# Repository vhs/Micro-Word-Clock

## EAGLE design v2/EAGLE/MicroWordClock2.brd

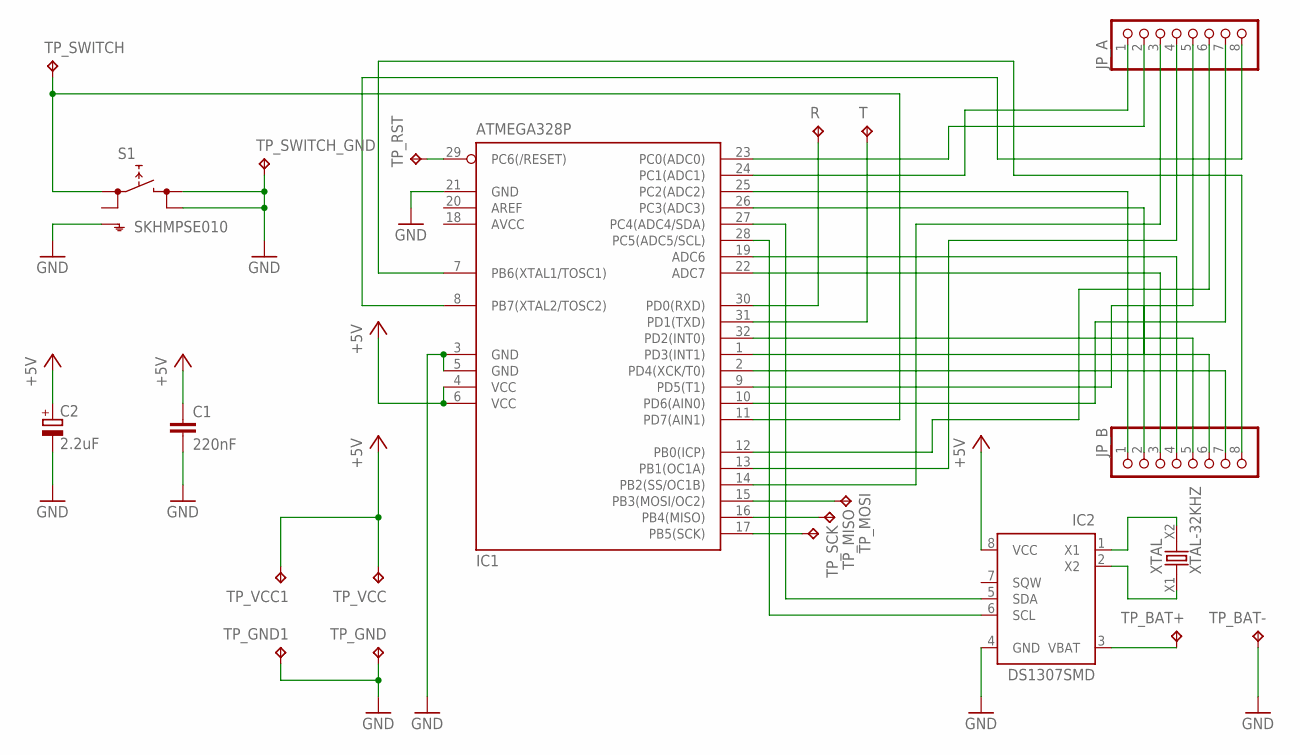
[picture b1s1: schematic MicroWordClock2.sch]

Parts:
C1: 220nF; C0805
C2: 2.2uF; B/3528-21R
IC1: ATMEGA328P; TQFP32-08
IC2: DS1307SMD; SO-08M
JP_A: PINHD-1X8CLEANBIG; 1X08-CLEANBIG
JP_B: PINHD-1X8CLEANBIG; 1X08-CLEANBIG
R: TPB1,27; B1,27
S1: SKHMPSE010; SKHMPXE010
T: TPB1,27; B1,27
TP_BAT+: TPB2,54; B2,54
TP_BAT-: TPB2,54; B2,54
TP_GND: TPB1,27; B1,27
TP_GND1: TPB2,54; B2,54
TP_MISO: TPB1,27; B1,27
TP_MOSI: TPB1,27; B1,27
TP_RST: TPB1,27; B1,27
TP_SCK: TPB1,27; B1,27
TP_SWITCH: TPB1,27; B1,27
TP_SWITCH_GND: TPB1,27; B1,27
TP_VCC: TPB1,27; B1,27
TP_VCC1: TPB2,54; B2,54
XTAL: XTAL-32KHZ; XTAL-SMD-1206-3216M

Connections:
+5V: C1.1, C2.+, IC1.4 (VCC), IC1.6 (VCC), IC2.8 (VCC), TP_VCC.TP, TP_VCC1.TP
A1: IC1.24 (PC1(ADC1)), JP_A.1
A2: IC1.23 (PC0(ADC0)), JP_A.2
A3: IC1.14 (PB2(SS/OC1B)), JP_A.3
A4: IC1.13 (PB1(OC1A)), JP_A.4
A5: IC1.9 (PD5(T1)), JP_A.5
A6: IC1.12 (PB0(ICP)), JP_A.6
A7: IC1.10 (PD6(AIN0)), JP_A.7
A8: IC1.8 (PB7(XTAL2/TOSC2)), JP_A.8
AVCC: IC1.18 (AVCC)
B1: IC1.25 (PC2(ADC2)), JP_B.1
B2: IC1.26 (PC3(ADC3)), JP_B.2
B3: IC1.22 (ADC7), JP_B.3
B4: IC1.19 (ADC6), JP_B.4
B5: IC1.32 (PD2(INT0)), JP_B.5
B6: IC1.1 (PD3(INT1)), JP_B.6
B7: IC1.2 (PD4(XCK/T0)), JP_B.7
B8: IC1.7 (PB6(XTAL1/TOSC1)), JP_B.8
GND: C1.2, C2.-, IC1.3 (GND), IC1.5 (GND), IC1.21 (GND), IC2.4 (GND), S1.3 (2.1), S1.4 (2.2), S1.5 (SH), TP_BAT-.TP, TP_GND.TP, TP_GND1.TP, TP_SWITCH_GND.TP
MISO: IC1.16 (PB4(MISO)), TP_MISO.TP
MOSI: IC1.15 (PB3(MOSI/OC2)), TP_MOSI.TP
unnamed: IC1.31 (PD1(TXD)), T.TP
unnamed: IC2.2 (X2), XTAL.X1
unnamed: IC1.30 (PD0(RXD)), R.TP
unnamed: IC2.1 (X1), XTAL.X2
unnamed: IC1.28 (PC5(ADC5/SCL)), IC2.6 (SCL)
RESET: IC1.29 (PC6(/RESET)), TP_RST.TP
SCK: IC1.17 (PB5(SCK)), TP_SCK.TP
SDA: IC1.27 (PC4(ADC4/SDA)), IC2.5 (SDA)
SWITCH: IC1.11 (PD7(AIN1)), S1.1 (1.1), TP_SWITCH.TP
VBAT: IC2.3 (VBAT), TP_BAT+.TP

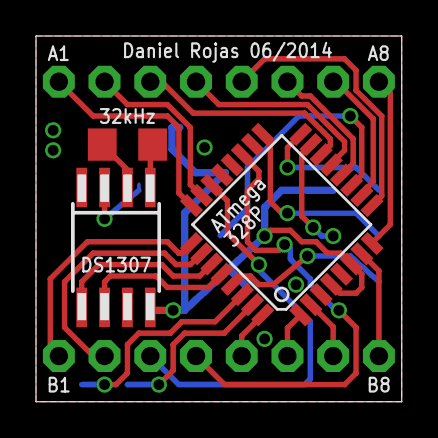
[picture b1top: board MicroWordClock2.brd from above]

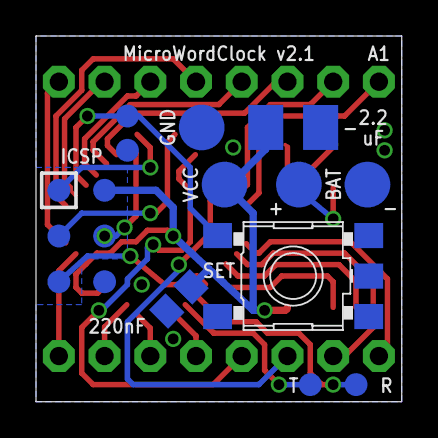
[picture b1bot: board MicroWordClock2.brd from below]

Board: 2 copper layers, 20.3 x 20.3 mm, 22 parts (17 on the bottom side), 30 nets.

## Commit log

2014-12-16 Changed schematic to free up serial port Widened all tracks to 12mil Panelised to put 9 onto a 5x5 "panel".
